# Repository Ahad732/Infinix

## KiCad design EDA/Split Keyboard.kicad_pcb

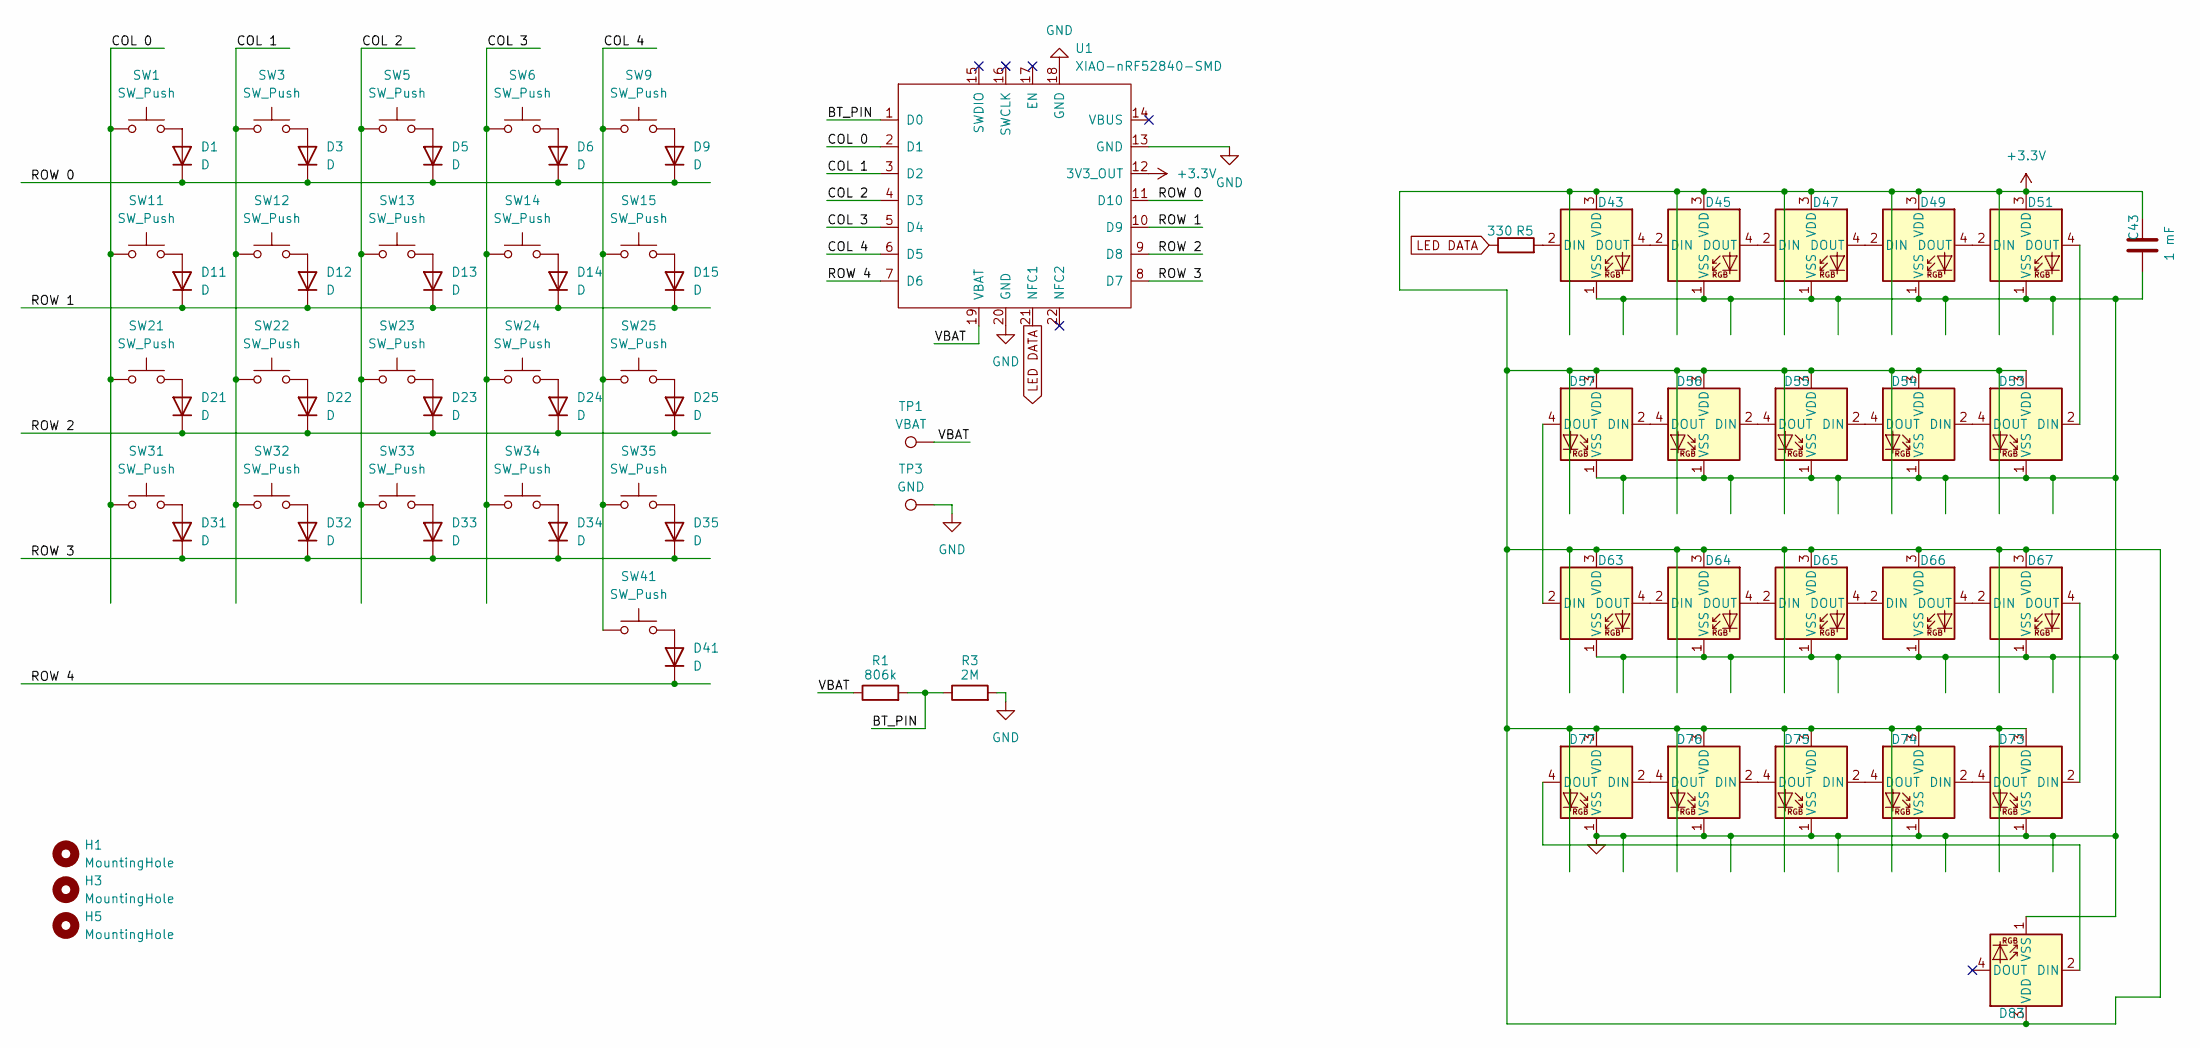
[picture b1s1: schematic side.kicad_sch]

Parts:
C43: 1 mF; CP_Elec_10x10
D1, D3, D5, D6, D9, D11, D12, D13, D14, D15, D21, D22, D23, D24, D25, D31, D32, D33, D34, D35, D41: D; D_SOD-123
D43, D45, D47, D49, D51, D53, D54, D55, D56, D57, D63, D64, D65, D66, D67, D73, D74, D75, D76, D77, D83: SK6812MINI-E; MX_SK6812MINI-E
H1, H3, H5: MountingHole; MountingHole_3.2mm_M3
R1: 806k; R_0603_1608Metric
R3: 2M; R_0805_2012Metric
R5: 330; R_1206_3216Metric
SW1, SW3, SW5, SW6, SW9, SW11, SW12, SW13, SW14, SW15, SW21, SW22, SW23, SW24, SW25, SW31, SW32, SW33, SW34, SW35, SW41: SW_Push; SW_Cherry_MX_1.00u_PCB
TP1: VBAT; TestPoint_Pad_D2.0mm
TP3: GND; TestPoint_Pad_D2.0mm
U1: XIAO-nRF52840-SMD

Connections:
+3.3V: C43.2, D43.3 (VDD), D45.3 (VDD), D47.3 (VDD), D49.3 (VDD), D51.3 (VDD), D53.3 (VDD), D54.3 (VDD), D55.3 (VDD), D56.3 (VDD), D57.3 (VDD), D63.3 (VDD), D64.3 (VDD), D65.3 (VDD), D66.3 (VDD), D67.3 (VDD), D73.3 (VDD), D74.3 (VDD), D75.3 (VDD), D76.3 (VDD), D77.3 (VDD), D83.3 (VDD), U1.12 (3V3_OUT); also elsewhere on the board
/left/BT_PIN: R1.2, R3.1, U1.1 (D0)
/left/COL 0: SW1.1, SW11.1, SW21.1, SW31.1, U1.2 (D1)
/left/COL 1: SW3.1, SW12.1, SW22.1, SW32.1, U1.3 (D2)
/left/COL 2: SW5.1, SW13.1, SW23.1, SW33.1, U1.4 (D3)
/left/COL 3: SW6.1, SW14.1, SW24.1, SW34.1, U1.5 (D4)
/left/COL 4: SW9.1, SW15.1, SW25.1, SW35.1, SW41.1, U1.6 (D5)
/left/ROW 0: D1.1 (K), D3.1 (K), D5.1 (K), D6.1 (K), D9.1 (K), U1.11 (D10)
/left/ROW 1: D11.1 (K), D12.1 (K), D13.1 (K), D14.1 (K), D15.1 (K), U1.10 (D9)
/left/ROW 2: D21.1 (K), D22.1 (K), D23.1 (K), D24.1 (K), D25.1 (K), U1.9 (D8)
/left/ROW 3: D31.1 (K), D32.1 (K), D33.1 (K), D34.1 (K), D35.1 (K), U1.8 (D7)
/left/ROW 4: D41.1 (K), U1.7 (D6)
/left/VBAT: R1.1, TP1.1 (1_1), U1.19 (VBAT)
GND: C43.1, D43.1 (VSS), D45.1 (VSS), D47.1 (VSS), D49.1 (VSS), D51.1 (VSS), D53.1 (VSS), D54.1 (VSS), D55.1 (VSS), D56.1 (VSS), D57.1 (VSS), D63.1 (VSS), D64.1 (VSS), D65.1 (VSS), D66.1 (VSS), D67.1 (VSS), D73.1 (VSS), D74.1 (VSS), D75.1 (VSS), D76.1 (VSS), D77.1 (VSS), D83.1 (VSS), R3.2, TP3.1 (1_1), U1.13 (GND), U1.18 (GND), U1.20 (GND); also elsewhere on the board
LED DATA: R5.1, U1.21 (NFC1); also elsewhere on the board
unnamed: D1.2 (A), SW1.2
unnamed: D3.2 (A), SW3.2
unnamed: D5.2 (A), SW5.2
unnamed: D6.2 (A), SW6.2
unnamed: D9.2 (A), SW9.2
unnamed: D11.2 (A), SW11.2
unnamed: D12.2 (A), SW12.2
unnamed: D13.2 (A), SW13.2
unnamed: D14.2 (A), SW14.2
unnamed: D15.2 (A), SW15.2
unnamed: D21.2 (A), SW21.2
unnamed: D22.2 (A), SW22.2
unnamed: D23.2 (A), SW23.2
unnamed: D24.2 (A), SW24.2
unnamed: D25.2 (A), SW25.2
unnamed: D31.2 (A), SW31.2
unnamed: D32.2 (A), SW32.2
unnamed: D33.2 (A), SW33.2
unnamed: D34.2 (A), SW34.2
unnamed: D35.2 (A), SW35.2
unnamed: D41.2 (A), SW41.2
unnamed: D43.2 (DIN), R5.2
unnamed: D43.4 (DOUT), D45.2 (DIN)
unnamed: D45.4 (DOUT), D47.2 (DIN)
unnamed: D47.4 (DOUT), D49.2 (DIN)
unnamed: D49.4 (DOUT), D51.2 (DIN)
unnamed: D51.4 (DOUT), D53.2 (DIN)
unnamed: D53.4 (DOUT), D54.2 (DIN)
unnamed: D54.4 (DOUT), D55.2 (DIN)
unnamed: D55.4 (DOUT), D56.2 (DIN)
unnamed: D56.4 (DOUT), D57.2 (DIN)
unnamed: D57.4 (DOUT), D63.2 (DIN)
unnamed: D63.4 (DOUT), D64.2 (DIN)
unnamed: D64.4 (DOUT), D65.2 (DIN)
unnamed: D65.4 (DOUT), D66.2 (DIN)
unnamed: D66.4 (DOUT), D67.2 (DIN)
unnamed: D67.4 (DOUT), D73.2 (DIN)
unnamed: D73.4 (DOUT), D74.2 (DIN)
unnamed: D74.4 (DOUT), D75.2 (DIN)
unnamed: D75.4 (DOUT), D76.2 (DIN)
unnamed: D76.4 (DOUT), D77.2 (DIN)
unnamed: D77.4 (DOUT), D83.2 (DIN)

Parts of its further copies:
C44: 1 mF; CP_Elec_10x10
D2, D4, D7, D8, D10, D16, D17, D18, D19, D20, D26, D27, D28, D29, D30, D36, D37, D38, D39, D40, D42: D; D_SOD-123
D44, D46, D48, D50, D52, D58, D59, D60, D61, D62, D68, D69, D70, D71, D72, D78, D79, D80, D81, D82, D84: SK6812MINI-E; MX_SK6812MINI-E
H2, H6: MountingHole; MountingHole_3.2mm_M3
R2: 806k; R_0603_1608Metric
R4: 2M; R_0805_2012Metric
R6: 330; R_1206_3216Metric
SW2, SW4, SW7, SW8, SW10, SW16, SW17, SW18, SW19, SW20, SW26, SW27, SW28, SW29, SW30, SW36, SW37, SW38, SW39, SW40, SW42: SW_Push; SW_Cherry_MX_1.00u_PCB
TP2: VBAT; TestPoint_Pad_D2.0mm
TP4: GND; TestPoint_Pad_D2.0mm
U2: XIAO-nRF52840-SMD

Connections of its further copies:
+3.3V: C44.2, D44.3 (VDD), D46.3 (VDD), D48.3 (VDD), D50.3 (VDD), D52.3 (VDD), D58.3 (VDD), D59.3 (VDD), D60.3 (VDD), D61.3 (VDD), D62.3 (VDD), D68.3 (VDD), D69.3 (VDD), D70.3 (VDD), D71.3 (VDD), D72.3 (VDD), D78.3 (VDD), D79.3 (VDD), D80.3 (VDD), D81.3 (VDD), D82.3 (VDD), D84.3 (VDD), U2.12 (3V3_OUT); also elsewhere on the board
/right/BT_PIN: R2.2, R4.1, U2.1 (D0)
/right/COL 0: SW2.1, SW16.1, SW26.1, SW36.1, U2.2 (D1)
/right/COL 1: SW4.1, SW17.1, SW27.1, SW37.1, U2.3 (D2)
/right/COL 2: SW7.1, SW18.1, SW28.1, SW38.1, U2.4 (D3)
/right/COL 3: SW8.1, SW19.1, SW29.1, SW39.1, U2.5 (D4)
/right/COL 4: SW10.1, SW20.1, SW30.1, SW40.1, SW42.1, U2.6 (D5)
/right/ROW 0: D2.1 (K), D4.1 (K), D7.1 (K), D8.1 (K), D10.1 (K), U2.11 (D10)
/right/ROW 1: D16.1 (K), D17.1 (K), D18.1 (K), D19.1 (K), D20.1 (K), U2.10 (D9)
/right/ROW 2: D26.1 (K), D27.1 (K), D28.1 (K), D29.1 (K), D30.1 (K), U2.9 (D8)
/right/ROW 3: D36.1 (K), D37.1 (K), D38.1 (K), D39.1 (K), D40.1 (K), U2.8 (D7)
/right/ROW 4: D42.1 (K), U2.7 (D6)
/right/VBAT: R2.1, TP2.1 (1_1), U2.19 (VBAT)
GND: C44.1, D44.1 (VSS), D46.1 (VSS), D48.1 (VSS), D50.1 (VSS), D52.1 (VSS), D58.1 (VSS), D59.1 (VSS), D60.1 (VSS), D61.1 (VSS), D62.1 (VSS), D68.1 (VSS), D69.1 (VSS), D70.1 (VSS), D71.1 (VSS), D72.1 (VSS), D78.1 (VSS), D79.1 (VSS), D80.1 (VSS), D81.1 (VSS), D82.1 (VSS), D84.1 (VSS), R4.2, TP4.1 (1_1), U2.13 (GND), U2.18 (GND), U2.20 (GND); also elsewhere on the board
LED DATA: R6.1, U2.21 (NFC1); also elsewhere on the board
unnamed: D2.2 (A), SW2.2
unnamed: D4.2 (A), SW4.2
unnamed: D7.2 (A), SW7.2
unnamed: D8.2 (A), SW8.2
unnamed: D10.2 (A), SW10.2
unnamed: D16.2 (A), SW16.2
unnamed: D17.2 (A), SW17.2
unnamed: D18.2 (A), SW18.2
unnamed: D19.2 (A), SW19.2
unnamed: D20.2 (A), SW20.2
unnamed: D26.2 (A), SW26.2
unnamed: D27.2 (A), SW27.2
unnamed: D28.2 (A), SW28.2
unnamed: D29.2 (A), SW29.2
unnamed: D30.2 (A), SW30.2
unnamed: D36.2 (A), SW36.2
unnamed: D37.2 (A), SW37.2
unnamed: D38.2 (A), SW38.2
unnamed: D39.2 (A), SW39.2
unnamed: D40.2 (A), SW40.2
unnamed: D42.2 (A), SW42.2
unnamed: D44.2 (DIN), R6.2
unnamed: D44.4 (DOUT), D46.2 (DIN)
unnamed: D46.4 (DOUT), D48.2 (DIN)
unnamed: D48.4 (DOUT), D50.2 (DIN)
unnamed: D50.4 (DOUT), D52.2 (DIN)
unnamed: D52.4 (DOUT), D58.2 (DIN)
unnamed: D58.4 (DOUT), D59.2 (DIN)
unnamed: D59.4 (DOUT), D60.2 (DIN)
unnamed: D60.4 (DOUT), D61.2 (DIN)
unnamed: D61.4 (DOUT), D62.2 (DIN)
unnamed: D62.4 (DOUT), D68.2 (DIN)
unnamed: D68.4 (DOUT), D69.2 (DIN)
unnamed: D69.4 (DOUT), D70.2 (DIN)
unnamed: D70.4 (DOUT), D71.2 (DIN)
unnamed: D71.4 (DOUT), D72.2 (DIN)
unnamed: D72.4 (DOUT), D78.2 (DIN)
unnamed: D78.4 (DOUT), D79.2 (DIN)
unnamed: D79.4 (DOUT), D80.2 (DIN)
unnamed: D80.4 (DOUT), D81.2 (DIN)
unnamed: D81.4 (DOUT), D82.2 (DIN)
unnamed: D82.4 (DOUT), D84.2 (DIN)

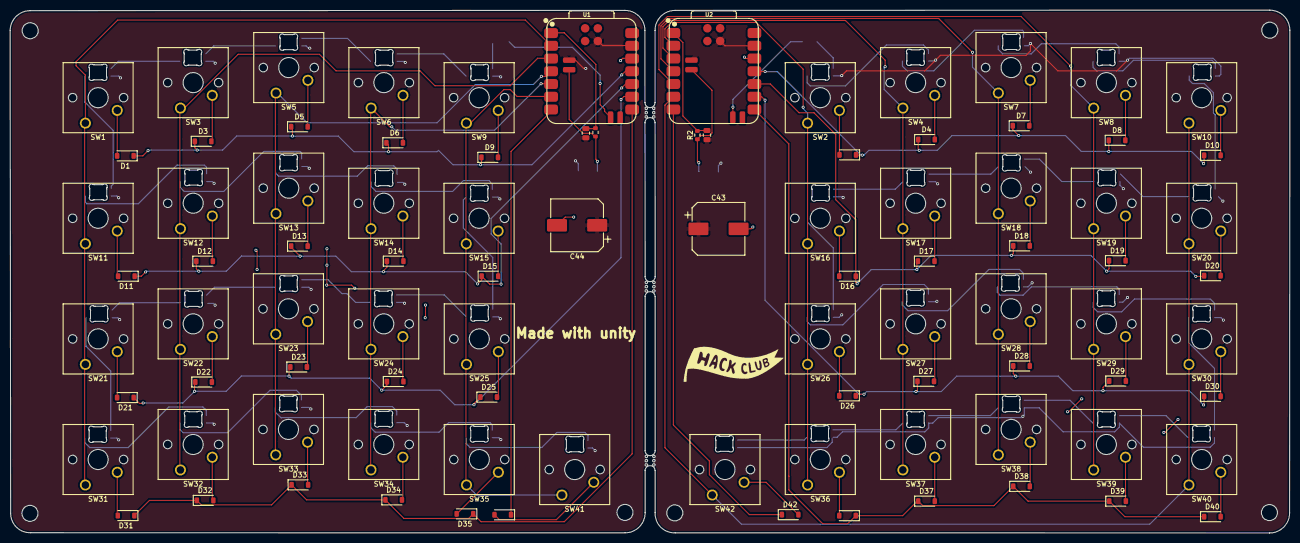
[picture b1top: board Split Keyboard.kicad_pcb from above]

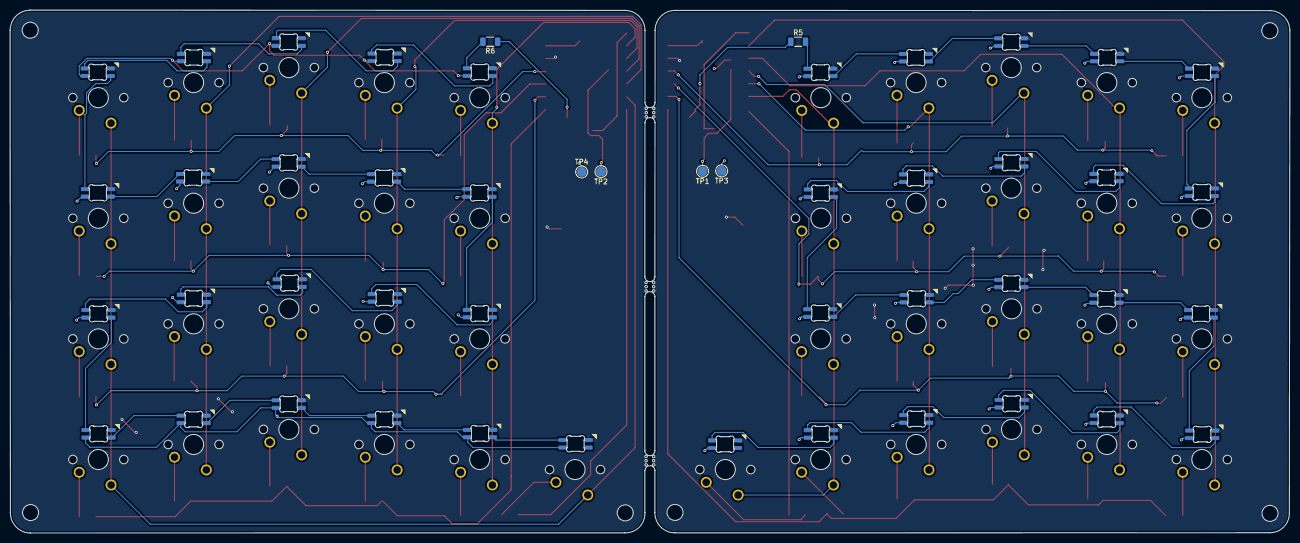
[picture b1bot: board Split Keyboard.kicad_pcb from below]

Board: 2 copper layers, 255.1 x 104.2 mm, 146 parts (6 on the bottom side), 111 nets.

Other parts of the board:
H5#2, H6#2: MountingHole; MountingHole_3.2mm_M3

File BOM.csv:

,Footprint,Value,Quantity,Price,Link
"C43, C44",CP_Elec_10x10,1 mF,3,0.28,https://robu.in/product/efvm016ada102m10b0-follon-1000uf-25v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
"D1, D10, D11, D12, D13, D14, D15, D16, D17, D18, D19, D2, D20, D21, D22, D23, D24, D25, D26, D27, D28, D29, D3, D30, D31, D32, D33, D34, D35, D36, D37, D38, D39, D4, D40, D41, D42, D5, D6, D7, D8, D9",D_SOD-123,D,50,0.5,https://robu.in/product/sm4007pl-a7-slkor-1a-1kv-1-1v1a-sod-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
"D43, D44, D45, D46, D47, D48, D49, D50, D51, D52, D53, D54, D55, D56, D57, D58, D59, D60, D61, D62, D63, D64, D65, D66, D67, D68, D69, D70, D71, D72, D73, D74, D75, D76, D77, D78, D79, D80, D81, D82, D83, D84",MX_SK6812MINI-E,SK6812MINI-E,51,5.55,https://www.etstore.in/products/e9974?variant=48993209319675
"R1, R2",603,806k,30,0.12,https://robu.in/product/0603waf8063t5e-uniohm-royal-ohm-100m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
"R3, R4",805,2M,15,0.11,https://robu.in/product/ac0805fr-072ml-yageo-res-thick-film-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
"R5, R6",1206,330,100,0.13,https://robu.in/product/1206w4j0331t5e-uniohm-royal-ohm-250m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
"SW1, SW10, SW11, SW12, SW13, SW14, SW15, SW16, SW17, SW18, SW19, SW2, SW20, SW21, SW22, SW23, SW24, SW25, SW26, SW27, SW28, SW29, SW3, SW30, SW31, SW32, SW33, SW34, SW35, SW36, SW37, SW38, SW39, SW4, SW40, SW41, SW42, SW5, SW6, SW7, SW8, SW9",SW_Cherry_MX_1.00u_PCB,SW_Push,1 pack of 45,11.52,https://stackskb.com/store/akko-v3-lavender-purple-pro-switc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
"U1, U2",XIAO-nRF52840-SMD,XIAO-nRF52840-SMD,2,24.06,https://www.lioncircuits.com/parts/102010448
,Keycaps,103 Key,1,10.47,https://www.amazon.in/gp/product/B0GZMBPHYB/ref=ox_sc_act_ti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
,Battery,1500 mAh,2,9.33,https://robu.in/product/wly103443-1500mah-3-7v-single-cell-r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
,,,Parts Shipping,2.93,
,,,PCB,39.33,
,,,Total,104.33,
